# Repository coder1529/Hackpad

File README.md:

# Hackpad

My first real hardware project — a 5-key macropad with a rotary encoder and a tiny OLED screen, built for Hack Club Stardance. I designed the whole thing from scratch: schematic, PCB, and the 3D printed case.

## What it actually is

A macropad is basically a mini keyboard just for shortcuts, so instead of digging through hotkey combos you tap one button and it's done. Mine has:

- 5 mechanical switches
- 1 rotary encoder with a click function, so it acts as a 6th button too
- A 0.91" I2C OLED screen
- A Seeed XIAO RP2040 running the whole thing
- A custom PCB with my dog on the silkscreen (non-negotiable)

## Status

Hardware side is finished — schematic's done, PCB is routed, and the case is modeled and ready to print. Firmware is next, haven't started coding it yet.

## Files

- `PCB folders/` — KiCad schematic and PCB layout
- `Macropad/` — KiCad project files
- `3d print folder/` — STL for the case

## Why I made this

I've done robotics and competitive programming for a while, but I'd never actually designed a PCB before, so this was my first time going from a blank schematic to something I could actually order and solder. Lots of "wait, why is this net not connecting" moments along the way. Shipping this for Stardance.

## IMAGES

### PCB

###
### 3D DESIGN

## BOM

| Ref | Part | Qty | Notes |
|---|---|---|---|
| U1 | Seeed Studio XIAO RP2040 | 1 | Main controller, USB-C |
| U2 | 0.91" I2C OLED display | 1 | Status screen |
| SW1, SW2, SW3, SW5, SW6 | Cherry MX-style switch, 1u, PCB mount | 5 | Keycaps not included |
| SW4 | ALPS EC11E rotary encoder w/ push | 1 | Doubles as a 6th button |
| — | Custom PCB | 1 | JLCPCB-manufacturable |
| — | 3D printed case | 1 | Single piece |

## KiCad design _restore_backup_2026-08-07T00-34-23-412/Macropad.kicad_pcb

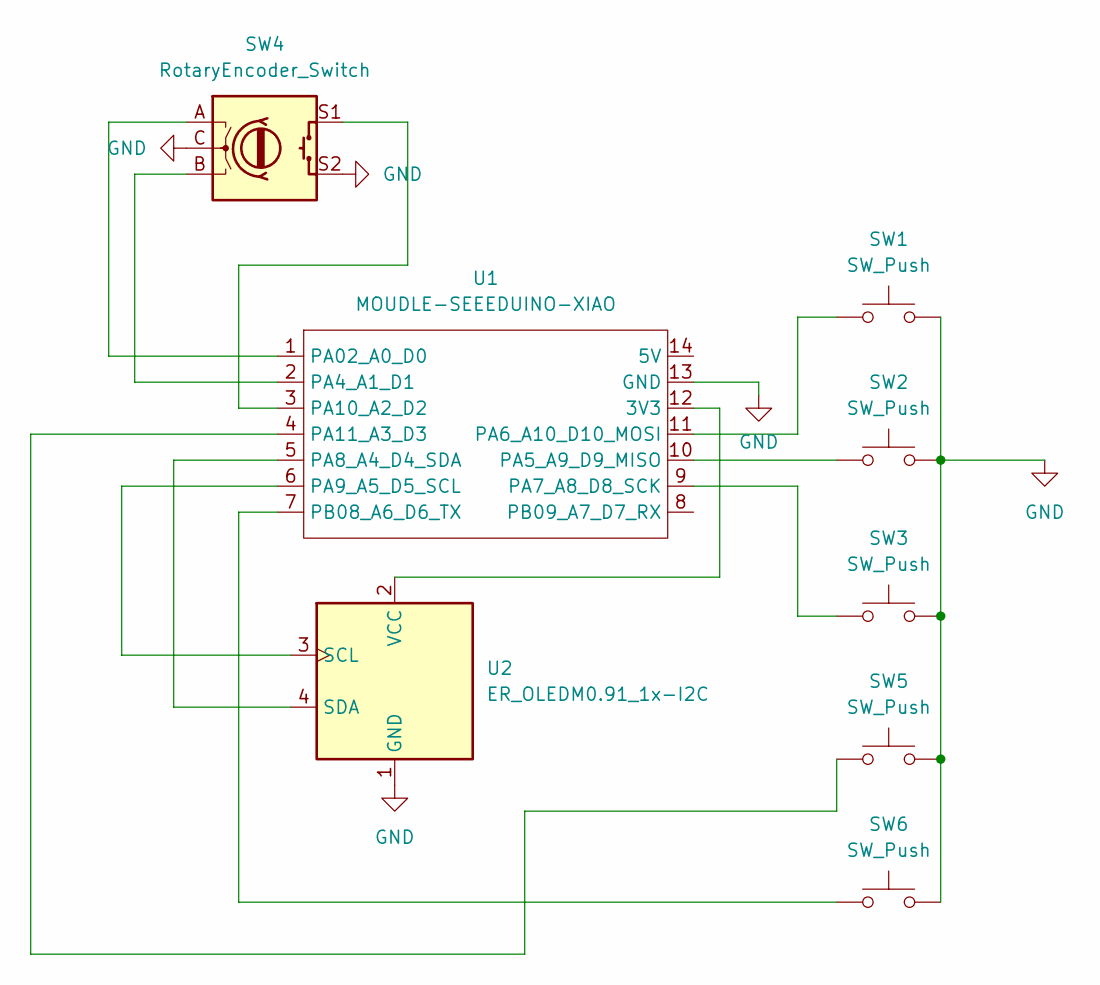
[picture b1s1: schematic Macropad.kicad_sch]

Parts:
SW1, SW2, SW3, SW5, SW6: SW_Push; SW_Cherry_MX_1.00u_PCB
SW4: RotaryEncoder_Switch; RotaryEncoder_Alps_EC11E-Switch_Vertical_H20mm_CircularMoun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
U1: MOUDLE-SEEEDUINO-XIAO; XIAO-Generic-Hybrid-14P-2.54-21X17.8MM
U2: ER_OLEDM0.91_1x-I2C

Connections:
GND: SW1.2, SW2.2, SW3.2, SW4.C, SW4.S2, SW5.2, SW6.2, U1.13 (GND), U2.1 (GND)
unnamed: U1.12 (3V3), U2.2 (VCC)
unnamed: SW4.A, U1.1 (PA02_A0_D0)
unnamed: SW4.B, U1.2 (PA4_A1_D1)
unnamed: SW2.1, U1.10 (PA5_A9_D9_MISO)
unnamed: SW1.1, U1.11 (PA6_A10_D10_MOSI)
unnamed: SW3.1, U1.9 (PA7_A8_D8_SCK)
unnamed: U1.5 (PA8_A4_D4_SDA), U2.4 (SDA)
unnamed: U1.6 (PA9_A5_D5_SCL), U2.3 (SCL)
unnamed: SW4.S1, U1.3 (PA10_A2_D2)
unnamed: SW5.1, U1.4 (PA11_A3_D3)
unnamed: SW6.1, U1.7 (PB08_A6_D6_TX)

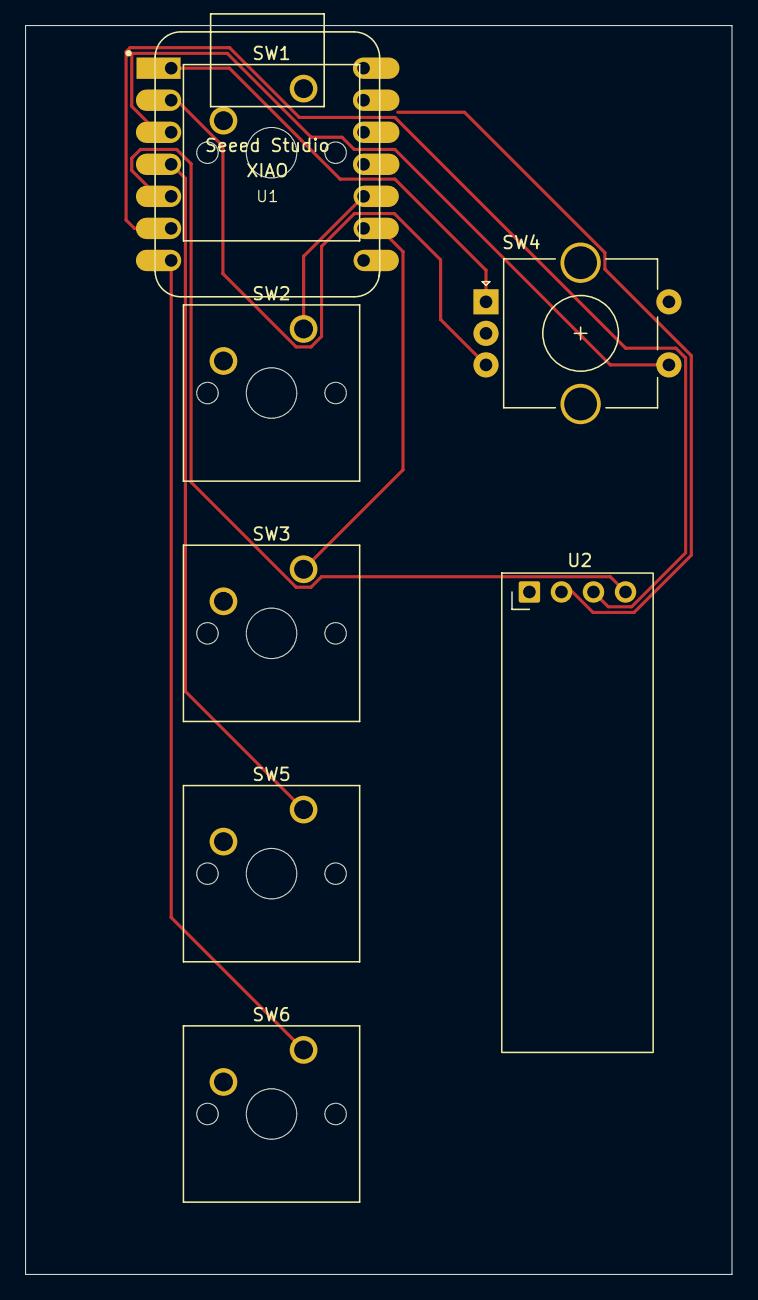
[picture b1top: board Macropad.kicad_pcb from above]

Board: 2 copper layers, 56.0 x 99.0 mm, 8 parts (0 on the bottom side), 12 nets.

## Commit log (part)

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2026-06-08 Add KiCad design files and wakatime config
